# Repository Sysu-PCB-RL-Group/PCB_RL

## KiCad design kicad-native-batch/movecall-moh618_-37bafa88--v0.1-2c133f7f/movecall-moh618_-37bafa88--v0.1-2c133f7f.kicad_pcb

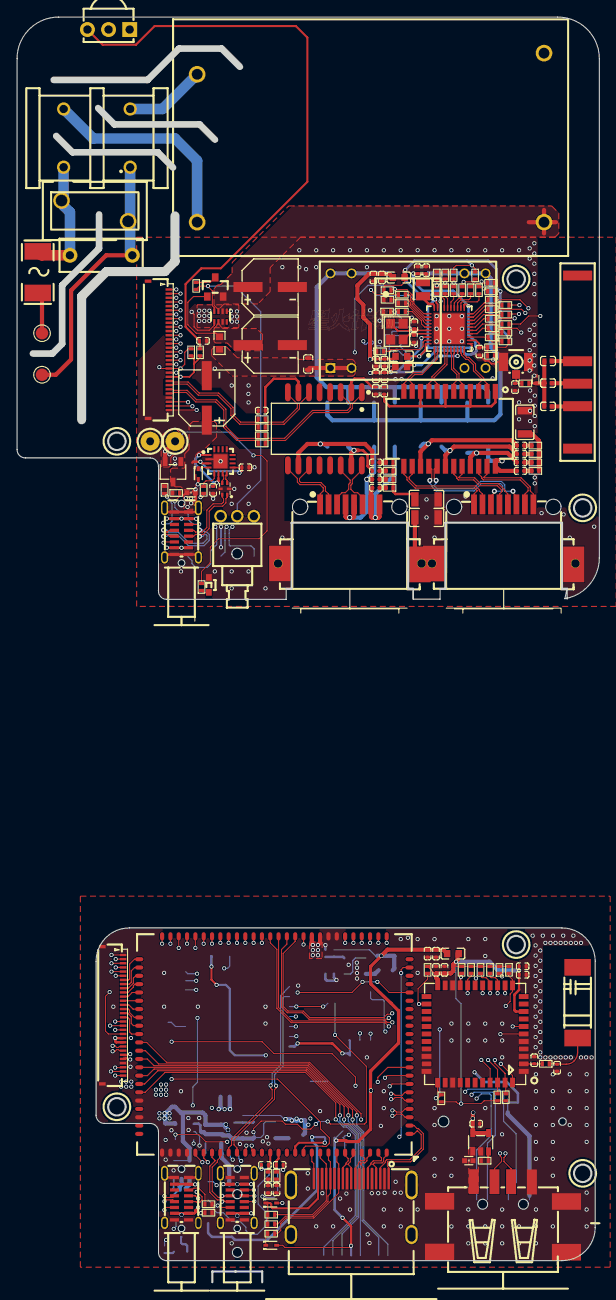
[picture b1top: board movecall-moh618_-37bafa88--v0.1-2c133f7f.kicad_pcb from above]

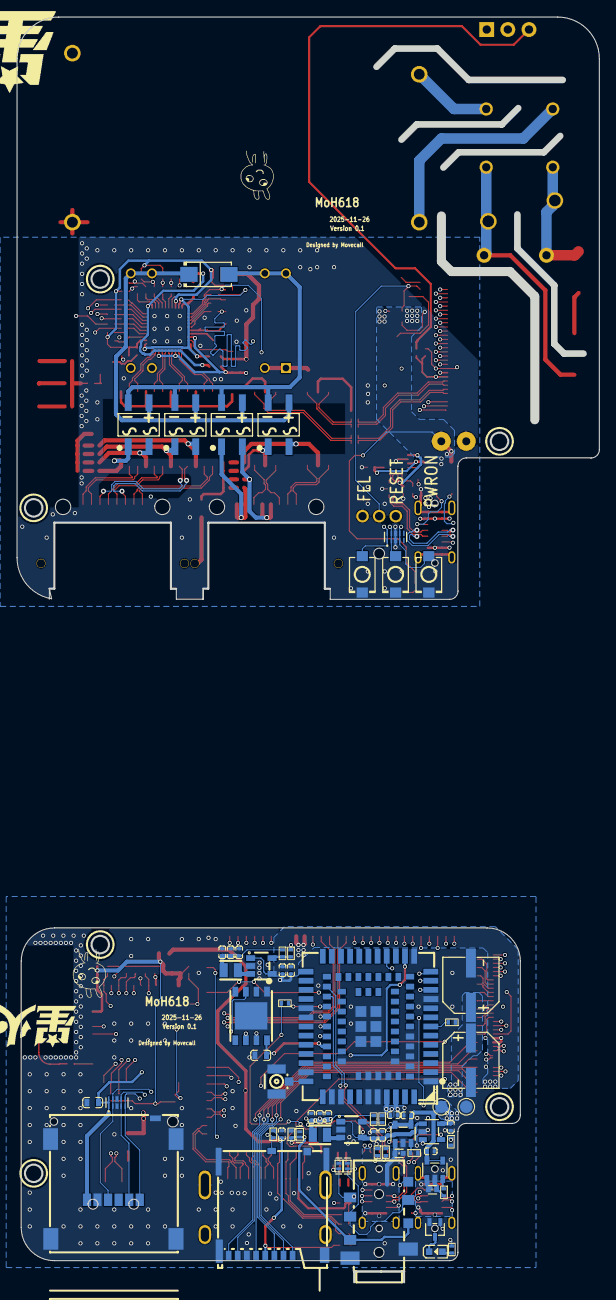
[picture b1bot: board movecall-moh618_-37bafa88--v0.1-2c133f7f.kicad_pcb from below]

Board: 4 copper layers, 70.0 x 152.1 mm, 233 parts (65 on the bottom side), 246 nets.

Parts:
ANT1: ANT-SMD_L23.0-W3.5
C1, C3, C4, C6, C7, C8, C9, C10, C11, C15, C18, C19, C20, C21, C22, C23, C24, C27, C28, C29, C30, C31, C32, C33, C35, C36, C37, C38, C39, C41, C42, C43, C44, C45, C46, C47, C48, C49, C50, C51, C52, C54, C55, C56, C57, C58, C59, C60, C61, C63, C64, C65, C66, C67: C0402
C2, C5, C25: C0603
C12, C13, C16, C17, C26: CAP-SMD_BD6.3-L6.6-W6.6-LS7.3-FD
C14: CAP-TH_L10.0-W4.0-P7.50-D0.5
C40, C53, C62: C1206
CARD1: TF-SMD_503398-1892
CN1, CN2: CONN-SMD_30P-P0.50_HCTL_HC-FPC-05-09-30RLTAG
CN3: AUDIO-SMD_PJ-393-8PJ
CN4, CN5: TESTPOINT-SMD_BD1.5-D0.8
D1, D2, D3, D4: X1SON-2_L1.0-W0.6-P0.65-BI
D5, D9, D10: SOD-523_L1.2-W0.8-LS1.6-RD
D6, D8, D11, D12: MBS_L4.8-W3.9-P2.5-LS6.7-BL
D7: SOT-23_L2.9-W1.3-P1.90-LS2.4-BR
D13, D14, D15: TSSLP-2-4_L1.0-W0.6-P0.65-BI
F1: F2410
HDMI1: HDMI-SMD_HDMI-001S
L1: IND-SMD_L1.0-W0.6
L2: IND-SMD_L1.0-W0.5-2
L3, L4: L0402
L5: FILTER-SMD_ICMEF112P900M-1
L6: FILTER-TH_4P-L17.0-W12.0-P7.00-D0.6-S8.00-1
L7, L10, L11, L12: L0603
L8: IND-SMD_L2.0-W1.6-B
L9: SMD-16_L12.7-W7.0-P1.27-LS9.5-BL
LED1: LED0603-RD
LED2: LED-SMD_L1.7-W0.6-RD
Q1: SOT-323-3_L2.0-W1.3-P1.30-LS2.1-BR
R1, R2, R3, R4, R5, R6, R7, R8, R9, R10, R11, R12, R14, R15, R16, R17, R18, R19, R20, R22, R23, R24, R25, R26, R27, R28, R29, R30, R31, R32, R33, R34, R35, R36, R37, R38, R39, R40, R41, R42, R43, R44, R45, R46, R47, R48, R49, R50, R51, R52, R53, R54, R55, R56, R57, R58, R59, R60, R61, R62, R63, R64, R65, R66, R67, R68, R69, R70, R71, R72, R73, R74, R75, R76, R78, R79, R80, R81, R82, R83, R84, R85, R88, R89: R0402
R13: RES-TH_L12.5-W7.0-P7.50-D1.2-S7.00
R21: R0603
RF1, RF2: ANT-SMD_2337019-1
RJ1, RJ2: RJ45-SMD_MJ88-B011-HLSV6-P
SIM1: SIM-SMD_NANO-SIM-6P
SW1: SW-TH_XKB5858-Z-C
SW2, SW3, SW4: SW-SMD_L3.9-W3.0-P4.45
SoM1: DS-H618
TP1, TP2, TP3, TP4: TESTPOINT_2MM
U1: LCC-LGA-109_L17.7-W15.8-P1.10_MC661
U2: UDFN-8_L6.0-W5.0-P1.27-TL-EP
U3: TQFN-16_L3.0-W3.0-P0.50-BL-EP1.7
U4, U19: DFN2510-10_L2.5-W1.0-P0.50-BL
U5, U14: TSOT-23-5_L2.9-W1.6-P0.95-LS2.8-BR
U6, U15: IND-SMD_L2.0-W1.6-B
U7, U10, U12, U17: SOT-23-5_L2.9-W1.6-P0.95-LS2.9-BL
U8: PWRM-TH_HLK-15M24
U9: SOT-23-3_L2.9-W1.6-P1.90-LS2.8-BR
U11: SOT-583-8_L2.1-W1.2-P0.50-LS1.6-BL
U13: PWRM-TH_DP9900LP-5V
U16: SMA_L4.3-W2.7-LS5.1-RD
U18: SMD-24_L15.1-W7.1-P1.00-LS10.0-BL
U20: QFN-40_L5.0-W5.0-P0.40-TL-EP3.7
U21: OPTO-TH_IRM-3638T
U22: ANT-SMD_L10.0-W3.2
U23: LGA-44_L12.0-W12.0-P0.90
USB1, USB2, USB3: USB-C-SMD_TYPEC-305-ACP16H458
USB4: USB-A-SMD_U-A-24SS-W-2
X1: CRYSTAL-SMD_4P-L2.5-W2.0-BL

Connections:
$1N1986: R9.1, USB1.B5
$1N1989: R5.2, USB1.A5
$1N5375: L9.16, RJ2.6
$1N5376: L9.14, RJ2.3
$1N5377: L9.11, RJ2.2
$1N5378: L9.9, RJ2.1
$1N5379: C53.2, RJ2.9
$1N5381: C57.1, R79.2
$1N5382: C58.1, R80.2
$1N5383: C59.1, R81.2
$1N5384: C60.1, R82.2
$1N5386: C62.2, R79.1, R80.1, R81.1, R82.1
$1N5389: L9.3, R71.1
$1N5391: L9.1, R64.1
$1N5394: L9.6, R72.1
$1N5395: L9.8, R73.1
$1N7528: C25.2, R21.1, U13.1, U13.2
$1N9324: C14.1, F1.2, L6.2, R13.2
$1N9348: C14.2, L6.1, R13.1, TP2.1
$1N10102: R10.1, USB2.B5
$1N10106: R6.2, USB2.A5
$1N10535: R7.2, USB3.A5
$1N10544: R11.1, USB3.B5
$1N12876: ANT1.1, L1.2
$1N12877: ANT1.2, L3.2
$1N12878: ANT1.3, L4.2
$1N12879: L1.1, L2.1, L3.1, L4.1, R1.2
$1N12882: C1.2, R1.1, RF1.2
$1N15014: C41.2, R54.1, U22.1
$1N17226: L6.3, U8.1
$1N17230: L6.4, U8.2
$1N17316: F1.1, TP1.1
$1N27914: C44.2, CN3.3, CN3.7, D14.2
$1N27920: C46.2, CN3.4, CN3.8, D13.2
$1N37538: RF2.2, U1.35
$1N44812: C40.2, R45.1, R46.1, R47.1, R48.1
$1N44814: C38.1, R48.2
$1N44815: C37.1, R47.2
$1N44816: C36.1, R46.2
$1N44817: C35.1, R45.2
$1N45482: D7.3, R20.1
$1N45622: LED2.2, R18.1
$1N46193: R17.1, U10.3
$1N46286: R14.1, U7.3
$1N46338: R22.1, U17.3
$1N46381: R19.1, U12.3
$1N47271: R8.2, U3.5
$1N47275: D5.1, U3.4
$1N47357: C4.2, U3.1, U3.6
$1N47640: C28.2, R30.2, U21.3
$1N51306: L5.3, U3.8
$1N51311: L5.4, U3.7
$1N51711: U5.3, U6.1
$1N51714: R15.2, R16.1, U5.5
$1N52088: R23.2, R24.2, U14.5
$1N52090: U14.3, U15.1
$1N52629: R2.2, U1.7
$1N52694: R4.1, U1.61
$1N52859: LED1.1, Q1.3
$1N52935: LED1.2, R3.1
$1N58460: C49.1, L9.2
$1N58529: C50.1, L9.7
$1N59188: C43.2, R58.1
$1N59224: C45.2, R62.1
$1N59714: D9.1, R25.1
$1N60108: C42.2, R54.2, U23.2
$1N76869: C38.2, D12.2, U18.15
$1N76874: C37.2, D12.1, U18.18
$1N76880: C36.2, D11.2, U18.21
$1N76886: C35.2, D11.1, U18.24
$1N77003: C39.2, U18.1, U18.4, U18.7, U18.10
$1N77307: R29.2, R32.2, U20.13
$1N77311: R28.2, R33.2, U20.14
$1N78218: L8.2, U20.30
$1N78259: C33.1, R34.2, R35.2, U20.12
$1N79066: C29.2, C30.1, L7.1, U20.3, U20.8, U20.38
$1N79358: R53.2, U20.39
$1N79764: R56.2, U20.25
$1N79766: R57.2, U20.24
$1N79768: R59.2, U20.23
$1N79770: R60.2, U20.22
$1N79772: R61.2, U20.27
$1N79774: R63.2, U20.26
$1N80359: R41.1, U20.15
$1N80361: R38.1, U20.16
$1N80363: R37.1, U20.17
$1N80365: R36.1, U20.18
$1N80441: R44.1, U20.19
$1N80443: R43.1, U20.20
+3V3: C6.1, C22.2, C23.2, C24.1, C54.1, C56.2, C63.2, C64.1, C65.1, C66.2, CARD1.4, CN1.21, CN1.22, CN2.21, CN2.22, D9.2, L10.1, L11.1, L12.1, R12.2, R24.1, R30.1, R31.2, U15.2
+3V9: C9.2, C10.2, C11.1, C12.1, C13.1, C67.1, R3.2, R16.2, U1.42, U1.43, U6.2
+AW3V3: C47.2, C48.1, C51.2, C52.1, L12.2, R50.2, R51.1, R52.1, R76.1, R78.1, R83.1, R84.1, R85.1, R88.1, R89.1, U23.9, U23.22
+H5V: D10.1, HDMI1.18, R26.2, R27.2
+IO3V3: L11.2, R28.1, R29.1, R35.1, R49.1, R65.1, R66.1, R67.1, U20.28
+PHY3V3: L10.2, R39.1, U20.11, U20.29, U20.40
+PHY10: C31.2, C32.1, L7.2, L8.1, U20.21
+POE: D6.3, D8.3, D11.3, D12.3, U13.5, U13.6, U16.1
-POE: D6.4, D8.4, D11.4, D12.4, U13.7, U13.8, U16.2
AP_CK32KO: R84.2, SoM1.38, U23.24
AP_WK_BT: SoM1.43, U23.6
BPI0: CN2.4, R60.1, R67.2
BPI1: CN2.3, R59.1, R68.2
BPI2: CN2.2, R57.1, R66.2
BPI3: CN2.1, R56.1, R65.2
BPI4: CN2.5, R61.1, R69.2
BPI5: CN2.6, R63.1, R70.2
BPI6: CN2.17, R34.1
BPI7: CN2.7, R41.2
BPI8: CN2.8, R38.2
BPI9: CN2.9, R37.2
BPI10: CN2.10, R36.2
BPI11: CN2.11, R43.2
BPI12: CN2.12, R44.2
BPI13: CN2.13, R74.2, R75.1
BPI14: CN2.14, R32.1
BPI15: CN2.15, R33.1
BPI16: CN2.16, R49.2, U20.31
BT_REG_ON: R78.2, SoM1.42, U23.34
BT_U_CTS: SoM1.36, U23.41
BT_U_RTS: SoM1.37, U23.44
BT_U_RX: R52.2, SoM1.35, U23.42
BT_U_TX: R51.2, SoM1.34, U23.43
BT_WK_AP: R50.1, SoM1.40, U23.7
CLKOUT: R75.2, U20.35
D1+: RJ1.1, U18.13
D1-: RJ1.2, U18.14
D2+: RJ1.3, U18.16
D2-: RJ1.6, U18.17
D3+: RJ1.4, U18.19
D3-: RJ1.5, U18.20
D4+: RJ1.7, U18.22
D4-: RJ1.8, U18.23
FEL: CN1.28, SoM1.7
FEL_: CN2.28, SW2.1, U19.1, U19.10
GND: C1.1, C2.1, C3.1, C4.1, C5.1, C6.2, C7.1, C8.1, C9.1, C10.1, C11.2, C12.2, C13.2, C15.2, C16.2, C17.2, C18.2, C19.2, C20.1, C21.1, C22.1, C23.1, C24.2, C25.1, C26.2, C27.2, C28.1, C29.1, C30.2, C31.1, C32.2, C33.2, C39.1, C40.1, C41.1, C42.1, C43.1, C45.1, C47.1, C48.2, C49.2, C50.2, C51.1, C52.2, C53.1, C54.2, C55.1, C56.1, C61.1, C62.1, C63.1, C64.2, C65.2, C66.1, C67.2, CARD1.6, CARD1.10, CARD1.11, CN1.27, CN1.31, CN1.32, CN2.27, CN2.31, CN3.1, CN3.5, CN5.1, D1.1, D2.1, D3.1, D4.1, D13.1, D14.1, D15.1, HDMI1.2, HDMI1.5, HDMI1.8, HDMI1.11, HDMI1.17, HDMI1.20, HDMI1.21, HDMI1.22, HDMI1.23, L2.2, L5.5, L5.6, LED2.1, Q1.2, R2.1, R5.1, R6.1, R7.1, R9.2, R10.2, R11.2, R14.2, R15.1, R17.2, R19.2, R22.2, R23.1, R40.1, R42.1, R53.1, R55.2, R68.1, R69.1, R70.1, R74.1, RF1.1, RF1.3, RF2.1, RF2.3, SIM1.1, SIM1.2, SIM1.3, SIM1.4, SIM1.5, SIM1.C5, SW1.3, SW2.2, SW3.2, SW4.2, SoM1.29, SoM1.30, SoM1.68, SoM1.70, SoM1.73, SoM1.74, SoM1.75, SoM1.76, TP4.1, U1.1, U1.10, U1.27, U1.34, U1.36, U1.37, U1.40, U1.41, U1.45, U1.46, U1.47, U1.48, U1.70, U1.71, U1.72, U1.73, U1.88, U1.89, U1.90, U1.91, U1.92, U1.93, U1.94, U1.95, U2.1, U2.9, U3.2, U3.17, U4.3, U4.8, U5.2, U7.2, U8.3, U9.1, U10.2, U11.1, U11.5, U12.2, U13.3, U14.2, U17.2, U19.3, U19.8, U20.0, U21.2, U23.1, U23.3, U23.5, U23.20, U23.31, U23.33, U23.36, USB1.1, USB1.A1, USB1.A12, USB1.B1, USB1.B12, USB2.1, USB2.A1, USB2.A12, USB2.B1, USB2.B12, USB3.1, USB3.A1, USB3.A12, USB3.B1, USB3.B12, USB4.4, USB4.5, USB4.6, X1.2, X1.4
H_0_N: HDMI1.9, SoM1.97
H_0_P: HDMI1.7, SoM1.98
H_1_N: HDMI1.6, SoM1.99
H_1_P: HDMI1.4, SoM1.100
H_2_N: HDMI1.3, SoM1.1
H_2_P: HDMI1.1, SoM1.2
H_CEC: HDMI1.13, R25.2, SoM1.94
H_C_N: HDMI1.12, SoM1.95
H_C_P: HDMI1.10, SoM1.96
H_HPD: HDMI1.19, SoM1.91
H_SCL: HDMI1.15, R26.1, SoM1.93
H_SDA: HDMI1.16, R27.1, SoM1.92
IR_RX: CN1.20, SoM1.18
IR_RX_: CN2.20, R31.1, U21.1
LINE_L: C44.1, R58.2, SoM1.86
LINE_R: C46.1, R62.2, SoM1.87
LTE_EN: SoM1.21, U12.4
NET_LED: Q1.1, U1.16
OFF/ON: R20.2, SW1.2, U11.4
PHY_L0: R39.2, U20.32
PHY_L1: R40.2, U20.33
PHY_L2: R42.2, U20.34
PI0: CN1.4, SoM1.44
PI1: CN1.3, SoM1.45
PI2: CN1.2, SoM1.46
PI3: CN1.1, SoM1.47
PI4: CN1.5, SoM1.48
PI5: CN1.6, SoM1.49
PI6: CN1.17, SoM1.50
PI7: CN1.7, SoM1.51
PI8: CN1.8, SoM1.52
PI9: CN1.9, SoM1.53
PI10: CN1.10, SoM1.54
PI11: CN1.11, SoM1.55
PI12: CN1.12, SoM1.56
PI13: CN1.13, SoM1.57
PI14: CN1.14, SoM1.58
PI15: CN1.15, SoM1.59
PI16: CN1.16, SoM1.60
PWRON: CN1.30, SoM1.33
PWRON_: CN2.30, SW4.1, U19.4, U19.7
RESET: CN1.29, SoM1.90
RESET_: CN2.29, SW3.1, U19.2, U19.9
RX_N: CN1.26, SoM1.3
RX_N_: CN2.26, R64.2
RX_P: CN1.25, SoM1.4
RX_P_: CN2.25, R71.2
SD_CLK: CARD1.5, SoM1.64
SD_CMD: CARD1.3, SoM1.65
SD_D0: CARD1.7, SoM1.63
SD_D1: CARD1.8, SoM1.62
SD_D2: CARD1.1, SoM1.67
SD_D3: CARD1.2, SoM1.66
SD_DET: CARD1.9, R12.1, SoM1.61
SIM2_CLK: U1.62, U2.6
SIM2_DAT: U1.64, U2.3
SIM2_RST: U1.63, U2.7
SIM2_VDD: C2.2, U1.65, U2.8
SIM_CLK: SIM1.C3, U1.13, U4.4, U4.7
SIM_DAT: SIM1.C7, U1.11, U4.5, U4.6
SIM_RST: SIM1.C2, U1.12, U4.2, U4.9
SIM_VDD: C5.2, SIM1.C1, U1.14, U4.1, U4.10
TRXN0: U18.11, U20.2
TRXN1: U18.8, U20.5
TRXN2: U18.5, U20.7
TRXN3: U18.2, U20.10
TRXP0: U18.12, U20.1
TRXP1: U18.9, U20.4
TRXP2: U18.6, U20.6
TRXP3: U18.3, U20.9
TV_OUT: CN3.2, CN3.6, D15.2, R55.1, SoM1.89
TX_N: CN1.24, SoM1.5
TX_N_: CN2.24, R72.2
TX_P: CN1.23, SoM1.6
TX_P_: CN2.23, R73.2
U0_RX: CN1.19, SoM1.9
U0_RX_: CN2.19, D5.2
U0_TX: CN1.18, SoM1.8
U0_TX_: CN2.18, R8.1
USB0_DN: SoM1.77, USB1.A7, USB1.B7
USB0_DP: SoM1.78, USB1.A6, USB1.B6
USB1_DN: SoM1.80, USB2.A7, USB2.B7
USB1_DP: SoM1.79, USB2.A6, USB2.B6
USB2_DN: SoM1.82, U1.60
USB2_DP: SoM1.81, U1.59
USB3_DN: SoM1.83, USB4.2
USB3_DP: SoM1.84, USB4.3
USB_N: L5.1, USB3.A7, USB3.B7
USB_P: L5.2, USB3.A6, USB3.B6
VA1: C58.2, D6.1, RJ2.7, RJ2.8
VA2: C57.2, D6.2, RJ2.4, RJ2.5
VB1: C59.2, D8.1, L9.15
VB2: C60.2, D8.2, L9.10
VBUS_D: C3.2, C17.1, D4.2, U3.3, U3.9, U9.3, USB3.A4, USB3.A9, USB3.B4, USB3.B9
VHLK_5V: C16.1, D7.2, U8.4, U11.3
VPOE_5V: C26.1, D7.1, R21.2, U11.6
VSW_5V: C15.1, C18.1, C19.1, C20.2, C21.2, C27.1, CN4.1, D10.2, R18.2, SoM1.31, SoM1.32, TP3.1, U7.4, U7.5, U9.2, U10.4, U10.5, U11.2, U11.7, U12.5, U14.1, U14.4, U17.4, U17.5
VUSB0_5V: D1.2, U7.1, USB1.A4, USB1.A9, USB1.B4, USB1.B9
VUSB1_5V: D2.2, U10.1, USB2.A4, USB2.A9, USB2.B4, USB2.B9
VUSB2_5V: C7.2, C8.2, R4.2, U5.1, U5.4, U12.1
VUSB3_5V: D3.2, U17.1, USB4.1
WL_REG_ON: R76.2, SoM1.41, U23.12
WL_SD_CLK: SoM1.24, U23.17
WL_SD_CMD: SoM1.26, U23.16
WL_SD_D0: R83.2, SoM1.27, U23.18
WL_SD_D1: R85.2, SoM1.25, U23.19
WL_SD_D2: R88.2, SoM1.28, U23.14
WL_SD_D3: R89.2, SoM1.23, U23.15
WL_WK_AP: SoM1.39, U23.13
XTAL_I: C61.2, U20.36, X1.1
XTAL_O: C55.2, U20.37, X1.3

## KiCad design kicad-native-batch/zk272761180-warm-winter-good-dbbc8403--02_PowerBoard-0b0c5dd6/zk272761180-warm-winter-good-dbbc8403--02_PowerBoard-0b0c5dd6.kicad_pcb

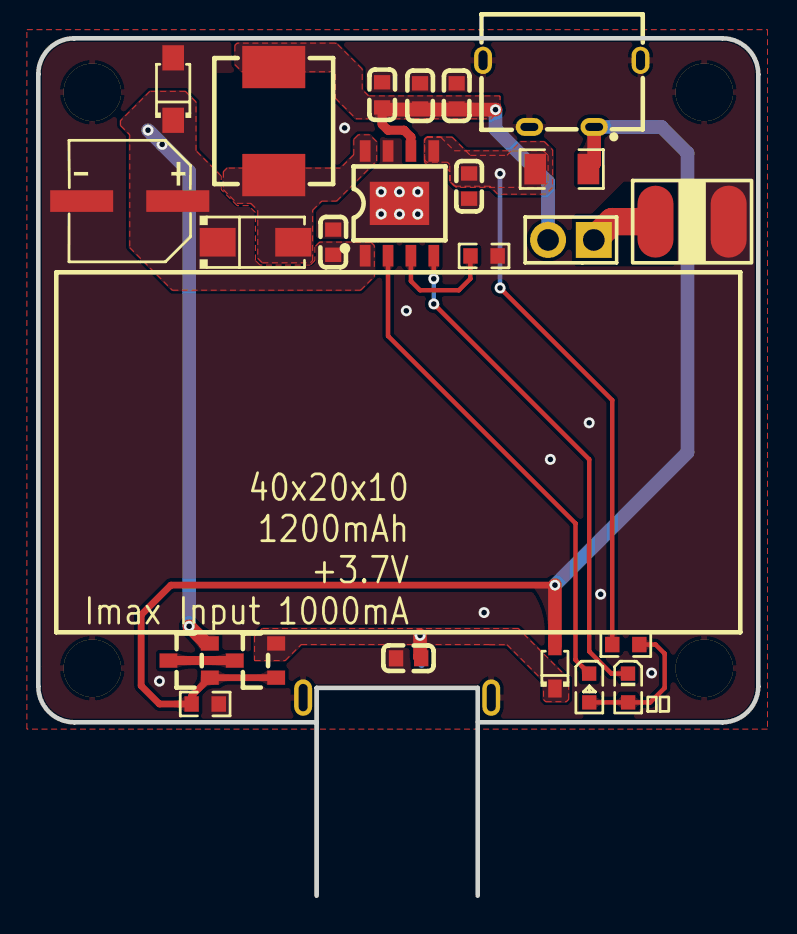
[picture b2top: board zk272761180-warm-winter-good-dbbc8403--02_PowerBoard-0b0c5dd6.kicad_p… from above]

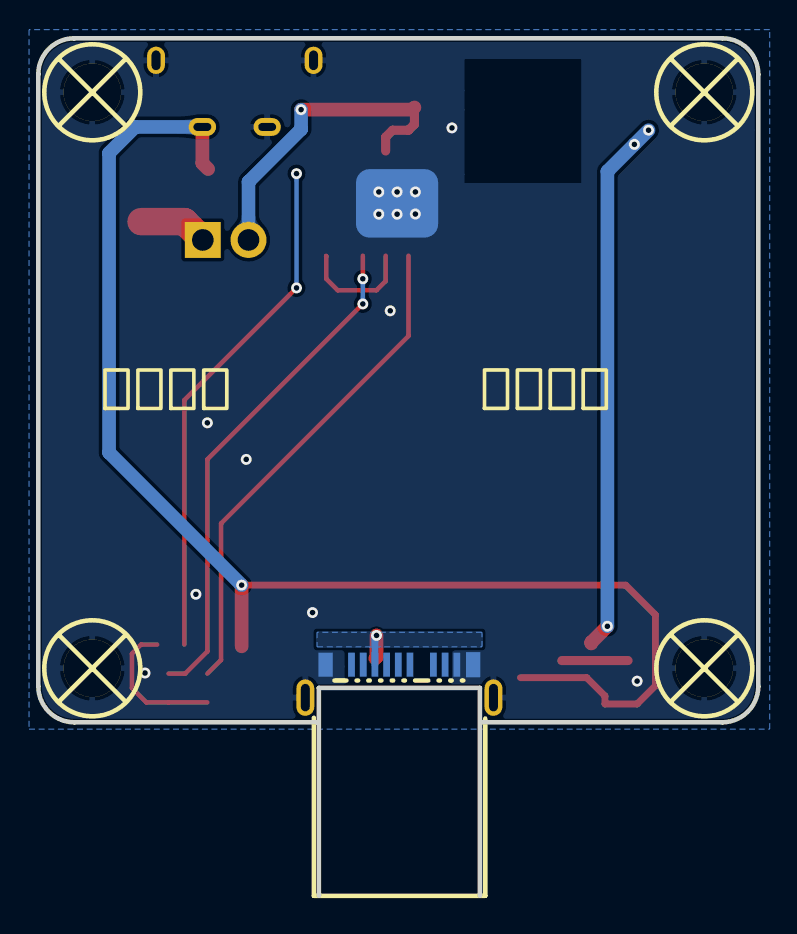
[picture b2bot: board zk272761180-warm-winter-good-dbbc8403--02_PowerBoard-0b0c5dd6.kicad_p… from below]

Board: 2 copper layers, 40.0 x 47.6 mm, 28 parts (5 on the bottom side), 13 nets.

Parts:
C1, C2, C3, C4, C5, C7: C0603
C6: CAP-SMD_BD6.3-L6.6-W6.6-LS7.2-FD
D1: SOD-123FL_L2.7-W1.8-LS3.8-RD
D2: SMA_L4.3-W2.5-LS5.0-RD
D3: SOD-323_L1.8-W1.3-LS2.5-RD
H1: HDR-TH_2P-P2.54-V-M
J1: BAT_2P
L1: IND-SMD_L7.3-W6.8
LED1: LED0603-RD_RED
LED2: LED0603-RD_GREEN
Q1, Q2: SOT-23_L2.9-W1.3-P1.90-LS2.4-BR
R1: R1206
R2, R3, R4: R0603
TP1, TP2, TP3, TP4: M3螺丝
U1: ESOP-8_L4.9-W3.9-P1.27-LS6.0-BL-EP
USB1: USB-SMD_KH-TYPE-C-2P
USB2: USB-TYPE-C-SMD_GT-USB-8016A

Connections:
$1N735: R3.1, U1.3
$1N738: D2.2, L1.2, U1.8
$1N746: C1.2, R1.2, R2.1, U1.5
$1N747: LED1.2, LED2.2, R2.2
$1N748: LED2.1, U1.4
$1N749: LED1.1, U1.2
$1N1719: Q1.3, Q2.3
$1N1883: H1.1, J1.1
GND: C1.1, C2.1, C3.1, C4.1, C5.1, C6.2, C7.1, D1.2, J1.2, R3.2, R4.2, TP1.1, TP2.1, TP3.1, TP4.1, U1.7, U1.9, USB1.2, USB1.3, USB1.4, USB2.1, USB2.2, USB2.3, USB2.4, USB2.A1
VBAT: C2.2, C3.2, C4.2, H1.2, L1.1, U1.6
VBAT5: C5.2, C6.1, D1.1, D2.1, Q1.2, U1.1
VIN5: D3.2, Q1.1, Q2.1, R1.1, R4.1, USB1.1
VOUT: C7.2, D3.1, Q2.2, USB2.A9
